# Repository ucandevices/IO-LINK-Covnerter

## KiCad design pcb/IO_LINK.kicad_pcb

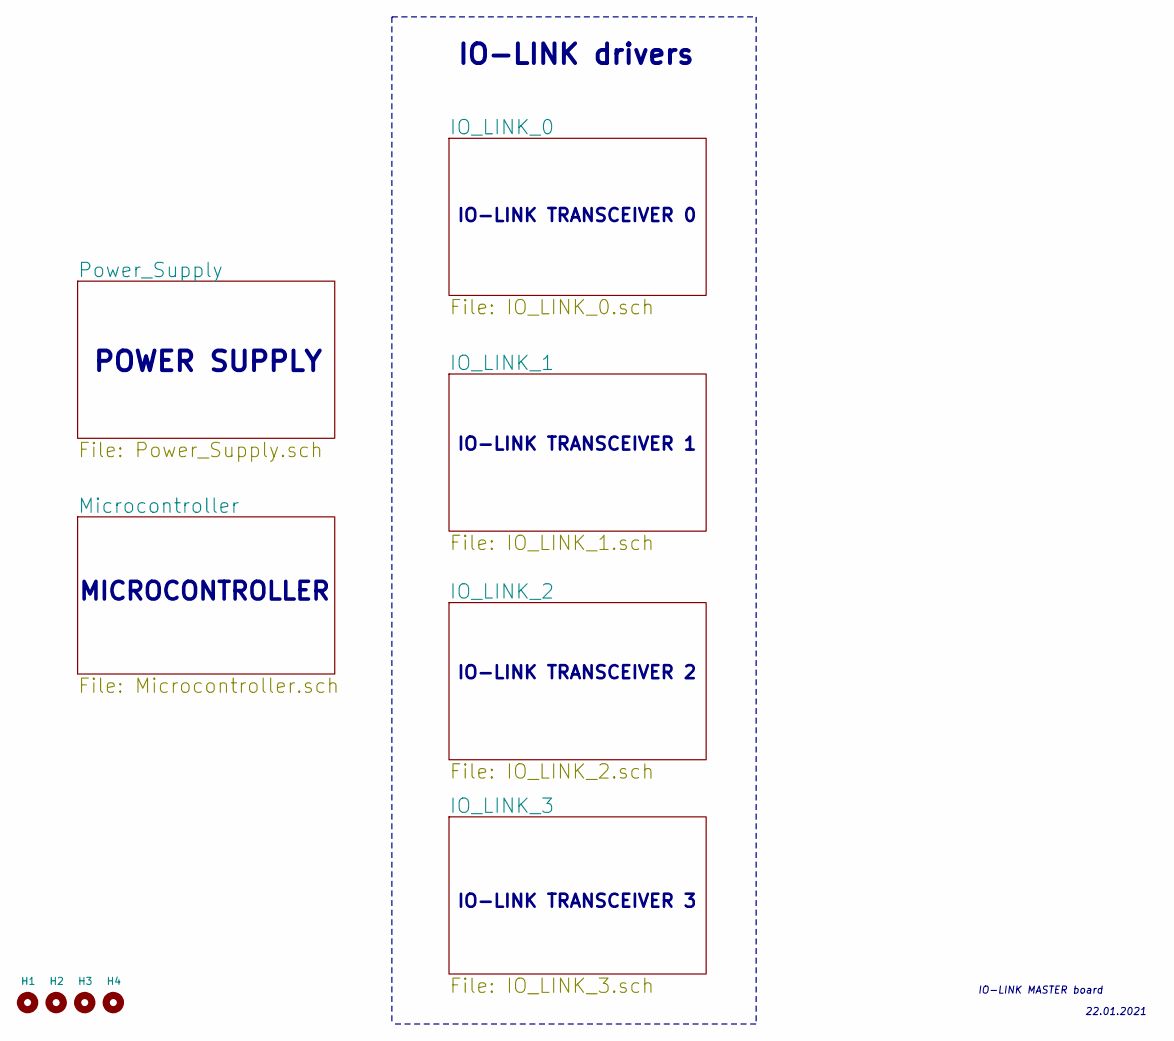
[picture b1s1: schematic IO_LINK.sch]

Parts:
H1, H2, H3, H4: MountingHole; MountingHole_3.2mm_M3_ISO14580_Pad_TopBottom

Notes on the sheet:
POWER SUPPLY
IO-LINK drivers
MICROCONTROLLER
IO-LINK TRANSCEIVER 0
IO-LINK TRANSCEIVER 1
IO-LINK TRANSCEIVER 2
IO-LINK TRANSCEIVER 3
IO-LINK MASTER board
22.01.2021

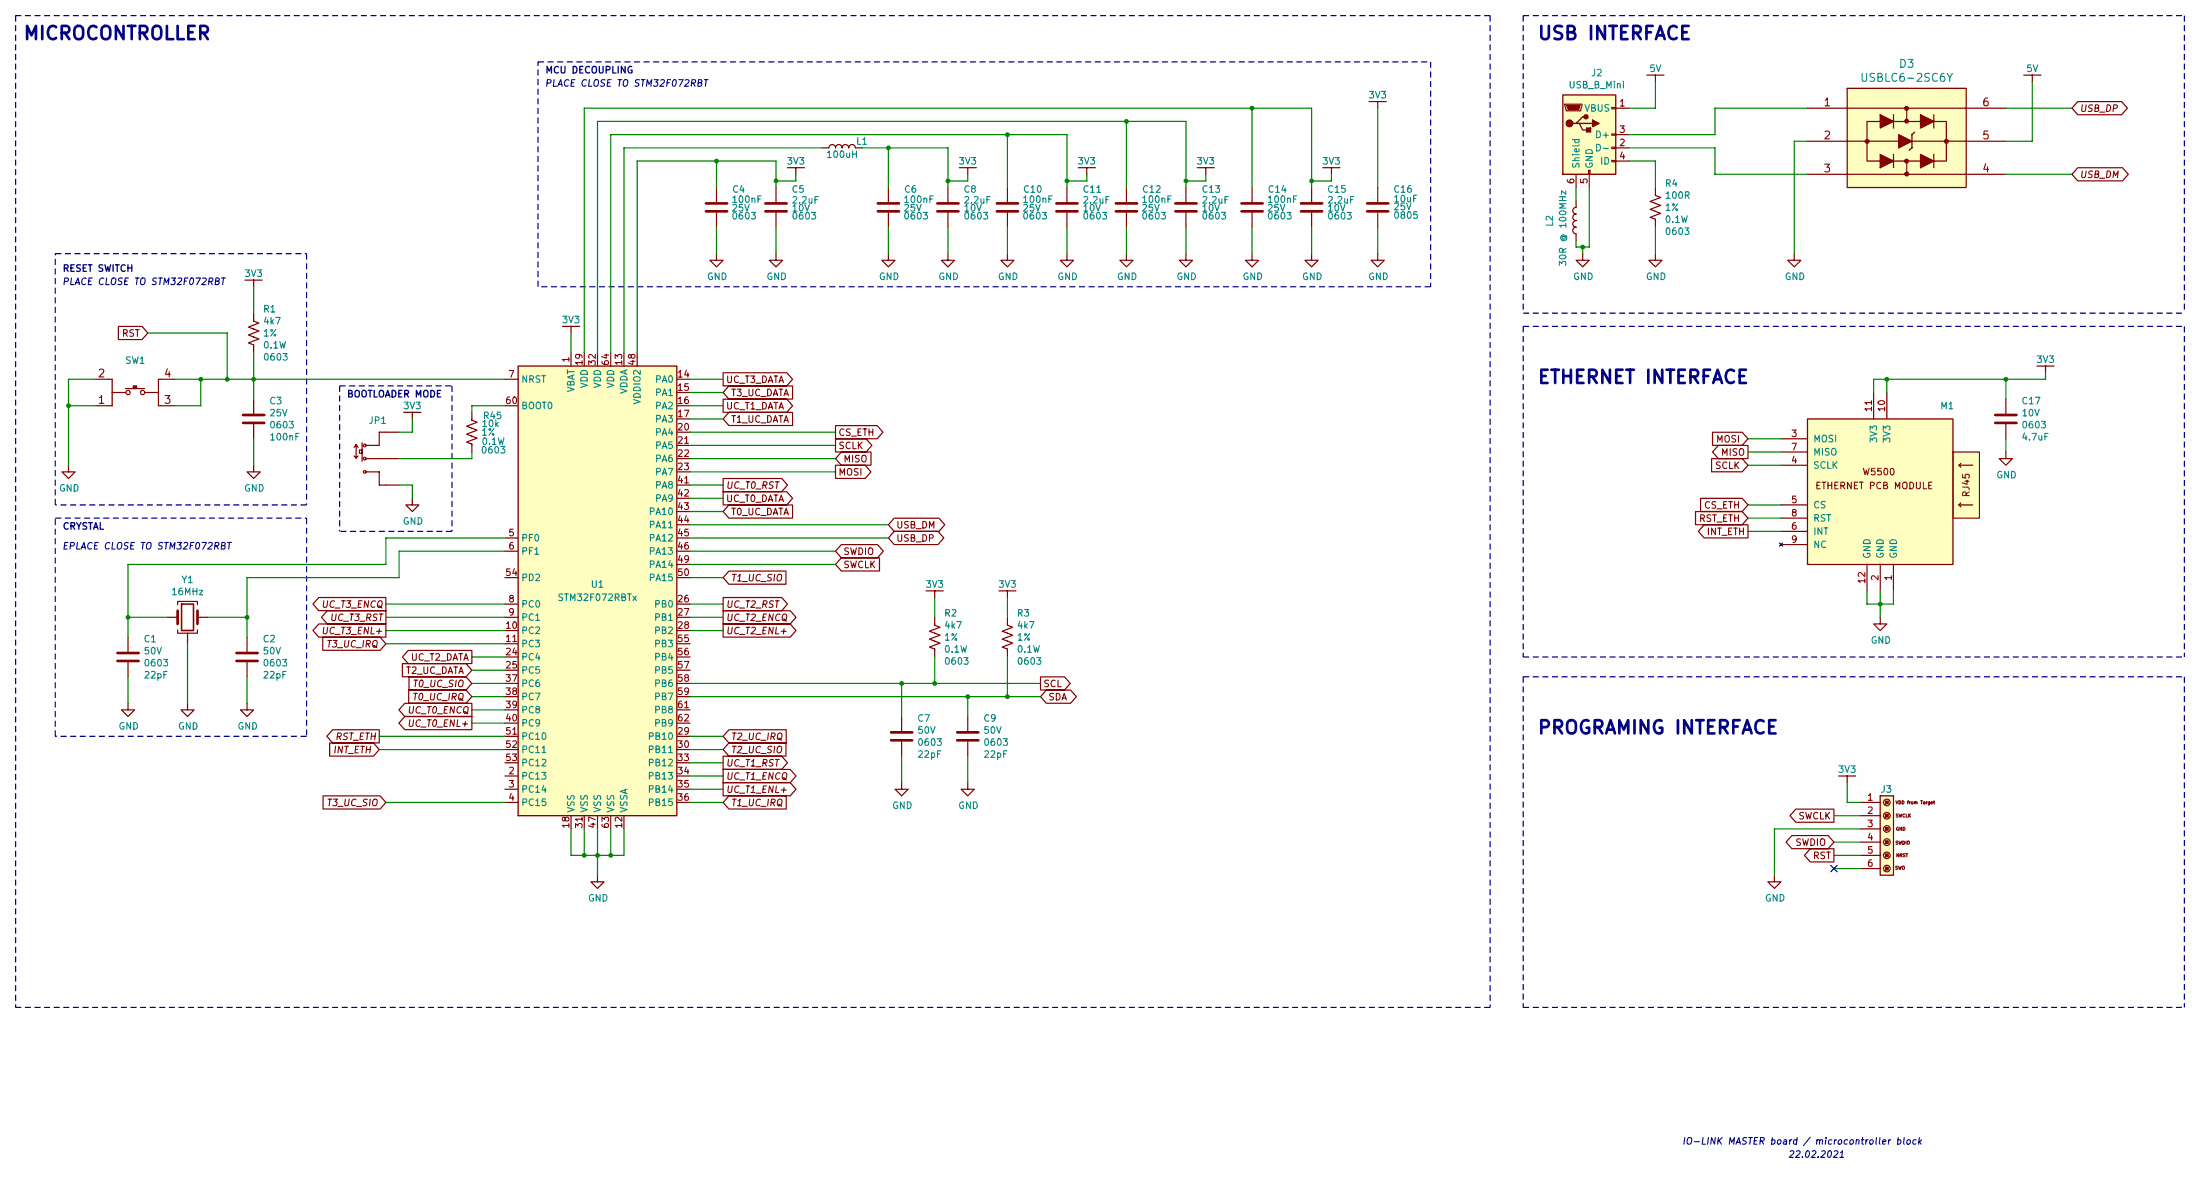
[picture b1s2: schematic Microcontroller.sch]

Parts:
C1, C2, C7, C9: 22pF_50V_0603; C_0603_1608Metric_Pad1.08x0.95mm_HandSolder; Voltage 50V; MPN CL10C220JB8NNNC; LCSC C1653
C3, C4, C6, C10, C12, C14: 100nF_25V_0603; C_0603_1608Metric_Pad1.08x0.95mm_HandSolder; Voltage 25V; MPN 0603B104K250CT; LCSC C83054
C5, C8, C11, C13, C15: 2.2uF_10V_0603; C_0603_1608Metric_Pad1.08x0.95mm_HandSolder; Voltage 10V; MPN CL10A225KP8NNNC; LCSC C1607
C16: 10uF_25V_0805; C_0805_2012Metric_Pad1.18x1.45mm_HandSolder; Voltage 25V; MPN CL21A106KAYNNNE; LCSC C15850
C17: 4.7uF_10V_0603; C_0603_1608Metric_Pad1.08x0.95mm_HandSolder; Voltage 10V; MPN CL10A475KP8NNNC; LCSC C1705
D3: USBLC6-2SC6Y; SOT-23-6L; MPN USBLC6-2SC6Y; LCSC C435848
J2: USB_B_Mini; USB_Mini-B_Horizontal; MPN 10033526-N3222MLF; LCSC N/A
J3: STM_PROGRAMING_CONNECTOR; MPN T821120A1S100CEU; LCSC N/A
JP1: SOLDERED_SELECTOR; SOLDERABLE_SELECTOR; MPN MCU08050Z0000ZP500; LCSC N/a
L1: Coil_100uH_0805; COIL_0805; MPN KLZ2012NHR101LTD25; LCSC N/A
L2: FB_30R@100MHz; Ferrite_bead_0603; MPN BLM18SP300SZ1D; LCSC N/A
M1: W5500_ETHERNET_PCB_MODULE; W5500_LITE_PCB_MODULE; MPN N/A; LCSC N/A
R1, R2, R3: 4k7_1%_0.1W_0603; R_0603_1608Metric_Pad0.98x0.95mm_HandSolder; Tolerance 1%; MPN 0603WAF4701T5E; LCSC C23162
R4: 100R_1%_0.1W_0603; R_0603_1608Metric_Pad0.98x0.95mm_HandSolder; Tolerance 1%; MPN 0603WAF1000T5E; LCSC C22775
R45: 10k_1%_0.1W_0603; R_0603_1608Metric_Pad0.98x0.95mm_HandSolder; Tolerance 1%; MPN 0603WAF1002T5E; LCSC C25804
SW1: Tactile_Switch; MPN PTS647SN50SMTR2LFS; LCSC N/A
U1: STM32F072RBTx; LQFP-64_10x10mm_P0.5mm
Y1: CRYSTAL_16MHz_4PADS; CRYSTAL_SMD_4PADS_3.2x2.5; MPN X322516MLB4SI; LCSC C13738

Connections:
3V3: C4.1, C5.1, C6.1, C8.1, C10.1, C11.1, C12.1, C13.1, C14.1, C15.1, C16.1, C17.1, J3.1, JP1.1, L1.2, M1.10 (3V3), M1.11 (3V3), R1.1, R2.1, R3.1, U1.1 (VBAT), U1.19 (VDD), U1.32 (VDD), U1.48 (VDDIO2), U1.64 (VDD); also elsewhere on the board
5V: D3.5, J2.1 (VBUS)
CS_ETH: M1.5 (CS), U1.20 (PA4)
GND: C1.2, C2.2, C3.2, C4.2, C5.2, C6.2, C7.2, C8.2, C9.2, C10.2, C11.2, C12.2, C13.2, C14.2, C15.2, C16.2, C17.2, D3.2, J2.5 (GND), J3.3, JP1.3, L2.1, M1.1 (GND), M1.2 (GND), M1.12 (GND), R4.2, SW1.1, SW1.2, U1.12 (VSSA), U1.18 (VSS), U1.31 (VSS), U1.47 (VSS), U1.63 (VSS), Y1.3; also elsewhere on the board
INT_ETH: M1.6 (INT), U1.52 (PC11)
MISO: M1.7 (MISO), U1.22 (PA6)
MOSI: M1.3 (MOSI), U1.23 (PA7)
unnamed: C1.1, U1.5 (PF0), Y1.1
unnamed: C2.1, U1.6 (PF1), Y1.2
unnamed: D3.1 (/IO), J2.3 (D+)
unnamed: D3.3 (2/IO), J2.2 (D-)
unnamed: J2.4 (ID), R4.1
unnamed: J2.6 (Shield), L2.2
unnamed: JP1.2, R45.2
unnamed: L1.1, U1.13 (VDDA)
unnamed: R45.1, U1.60 (BOOT0)
RST: C3.1, J3.5, R1.2, SW1.3, SW1.4, U1.7 (NRST)
RST_ETH: M1.8 (RST), U1.51 (PC10)
SCL: C7.1, R2.2, U1.58 (PB6); also elsewhere on the board
SCLK: M1.4 (SCLK), U1.21 (PA5)
SDA: C9.1, R3.2, U1.59 (PB7); also elsewhere on the board
SWCLK: J3.2, U1.49 (PA14)
SWDIO: J3.4, U1.46 (PA13)
T0_UC_DATA: U1.43 (PA10); also elsewhere on the board
T0_UC_IRQ: U1.38 (PC7); also elsewhere on the board
T0_UC_SIO: U1.37 (PC6); also elsewhere on the board
T1_UC_DATA: U1.17 (PA3); also elsewhere on the board
T1_UC_IRQ: U1.36 (PB15); also elsewhere on the board
T1_UC_SIO: U1.50 (PA15); also elsewhere on the board
T2_UC_DATA: U1.25 (PC5); also elsewhere on the board
T2_UC_IRQ: U1.29 (PB10); also elsewhere on the board
T2_UC_SIO: U1.30 (PB11); also elsewhere on the board
T3_UC_DATA: U1.15 (PA1); also elsewhere on the board
T3_UC_IRQ: U1.11 (PC3); also elsewhere on the board
T3_UC_SIO: U1.4 (PC15); also elsewhere on the board
UC_T0_DATA: U1.42 (PA9); also elsewhere on the board
UC_T0_ENCQ: U1.39 (PC8); also elsewhere on the board
UC_T0_ENL+: U1.40 (PC9); also elsewhere on the board
UC_T0_RST: U1.41 (PA8); also elsewhere on the board
UC_T1_DATA: U1.16 (PA2); also elsewhere on the board
UC_T1_ENCQ: U1.34 (PB13); also elsewhere on the board
UC_T1_ENL+: U1.35 (PB14); also elsewhere on the board
UC_T1_RST: U1.33 (PB12); also elsewhere on the board
UC_T2_DATA: U1.24 (PC4); also elsewhere on the board
UC_T2_ENCQ: U1.27 (PB1); also elsewhere on the board
UC_T2_ENL+: U1.28 (PB2); also elsewhere on the board
UC_T2_RST: U1.26 (PB0); also elsewhere on the board
UC_T3_DATA: U1.14 (PA0); also elsewhere on the board
UC_T3_ENCQ: U1.8 (PC0); also elsewhere on the board
UC_T3_ENL+: U1.10 (PC2); also elsewhere on the board
UC_T3_RST: U1.9 (PC1); also elsewhere on the board
USB_DM: D3.4 (2/IO), U1.44 (PA11)
USB_DP: D3.6 (1/IO), U1.45 (PA12)

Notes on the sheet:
USB INTERFACE
ETHERNET INTERFACE
RESET SWITCH
PROGRAMING INTERFACE
PLACE CLOSE TO STM32F072RBT
EPLACE CLOSE TO STM32F072RBT
CRYSTAL
MCU DECOUPLING
BOOTLOADER MODE
MICROCONTROLLER
IO-LINK MASTER board / microcontroller block
22.02.2021

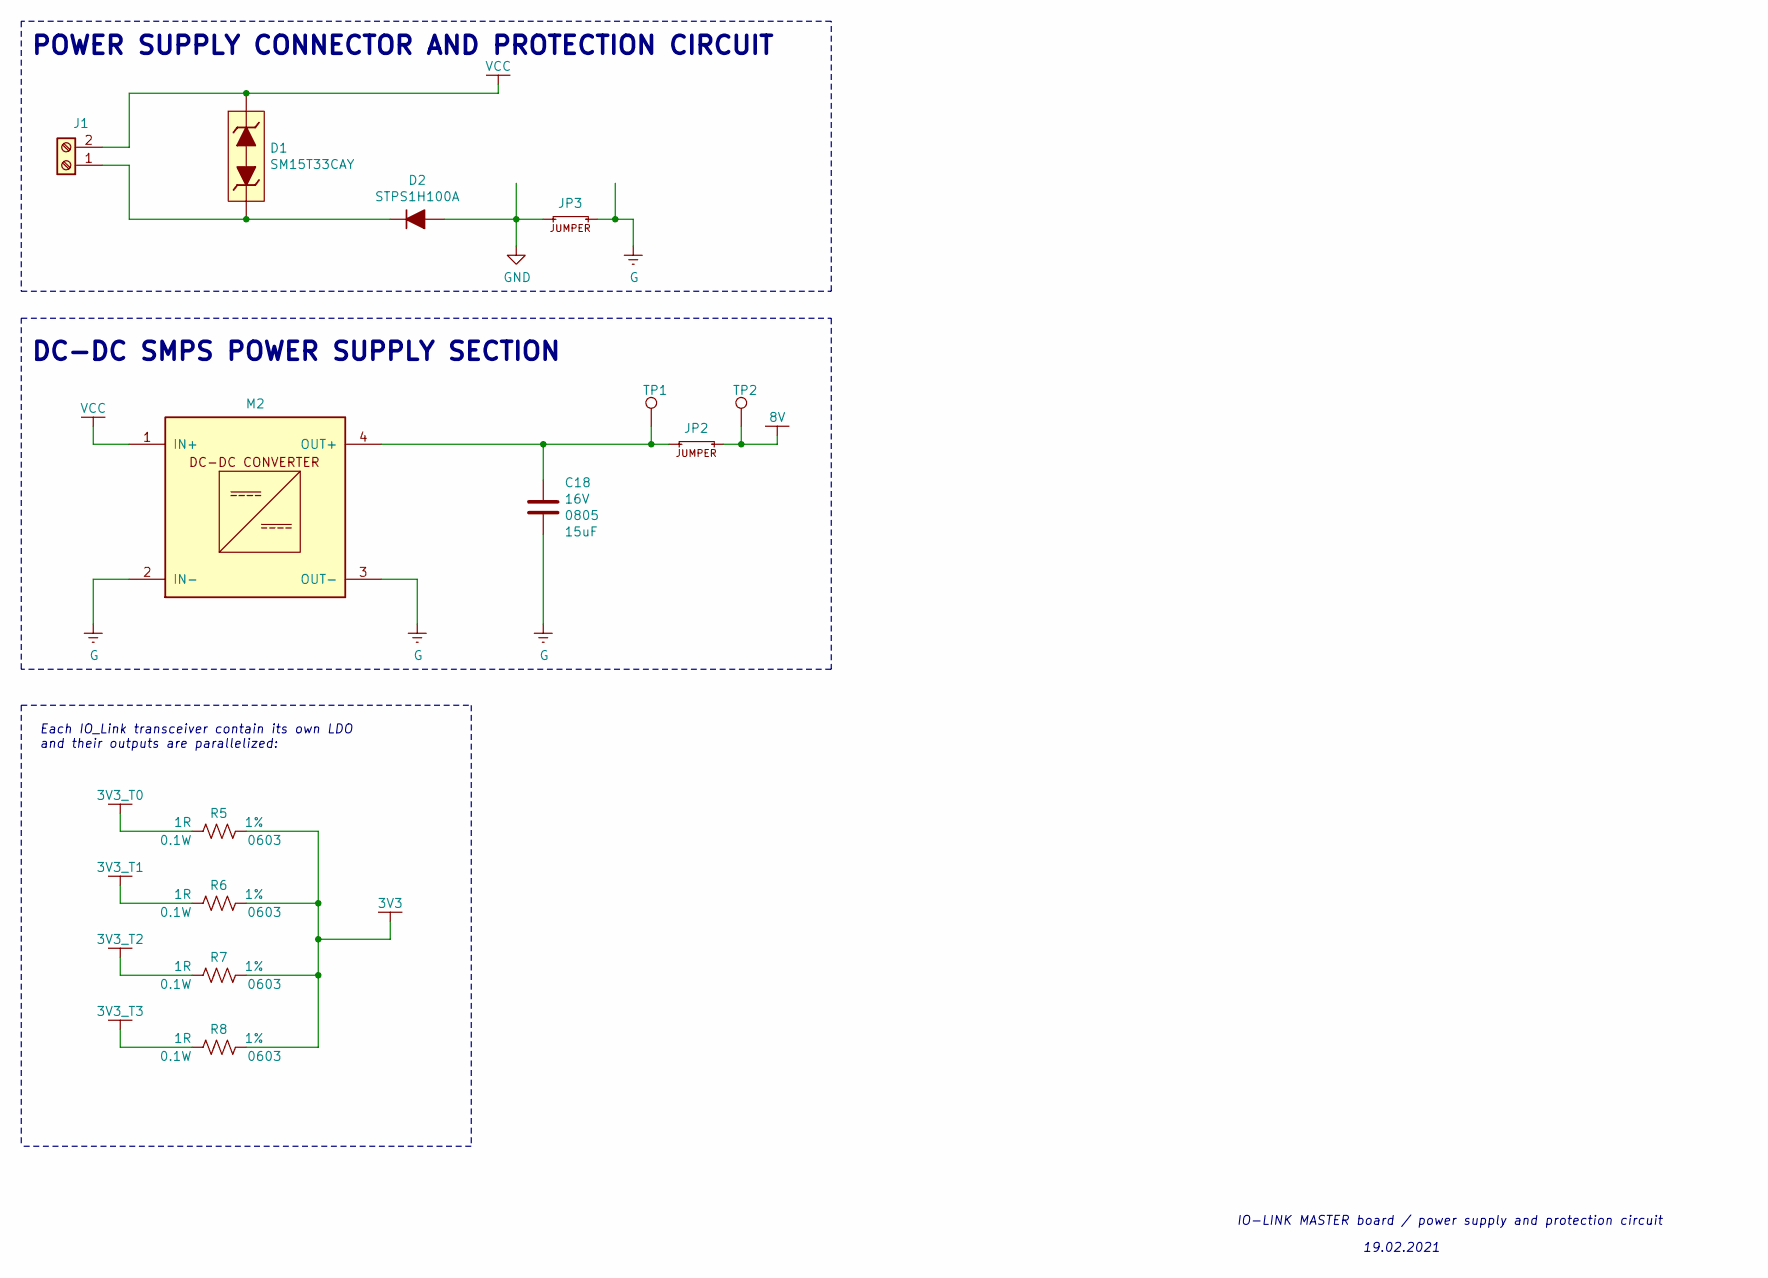
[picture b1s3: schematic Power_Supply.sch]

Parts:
C18: 15uF_16V_0805; C_0805_2012Metric_Pad1.18x1.45mm_HandSolder; Voltage 16V; MPN C2012JB1C156M125AC; LCSC N/A
D1: SM15T33CAY; SMC_BI_TVS; MPN SM15T33CAY; LCSC N/A
D2: STPS1H100A; SMA; MPN STPS1H100A; LCSC N/A
J1: Screw_Terminal_01x02; TerminalBlock_Altech_AK300-2_P5.00mm; MPN 1729128; LCSC N/A
JP2: 0R_1%_0.1W_0805; R_0805_2012Metric_Pad1.20x1.40mm_HandSolder; Tolerance 1%; MPN 0805W8F0000T5E; LCSC C17477
JP3: JUMPER_0805; R_0805_2012Metric_Pad1.20x1.40mm_HandSolder; Tolerance 1%; MPN 0805W8F0000T5E; LCSC C17477
M2: DC_DC_CONVERTER_LM2596_PCB_MODULE; MPN N/A; LCSC N/A
R5, R6, R7, R8: 1R_1%_0.1W_0603; R_0603_1608Metric_Pad0.98x0.95mm_HandSolder; Tolerance 1%; MPN 0603WAF100KT5E; LCSC C22936
TP1, TP2: TestPoint; TestPoint_Pad_D2.0mm

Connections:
3V3: R5.2, R6.2, R7.2, R8.2; also elsewhere on the board
3V3_T0: R5.1; also elsewhere on the board
3V3_T1: R6.1; also elsewhere on the board
3V3_T2: R7.1; also elsewhere on the board
3V3_T3: R8.1; also elsewhere on the board
8V: JP2.2, TP2.1; also elsewhere on the board
G: C18.2, JP3.2, M2.2 (IN-), M2.3 (OUT-); also elsewhere on the board
GND: D2.2 (A), JP3.1; also elsewhere on the board
unnamed: C18.1, JP2.1, M2.4 (OUT+), TP1.1
unnamed: D1.1, D2.1 (K), J1.1
VCC: D1.2, J1.2, M2.1 (IN+); also elsewhere on the board

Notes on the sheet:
POWER SUPPLY CONNECTOR AND PROTECTION CIRCUIT
IO-LINK MASTER board / power supply and protection circuit
19.02.2021
DC-DC SMPS POWER SUPPLY SECTION
Each IO_Link transceiver contain its own LDO and their outputs are parallelized:

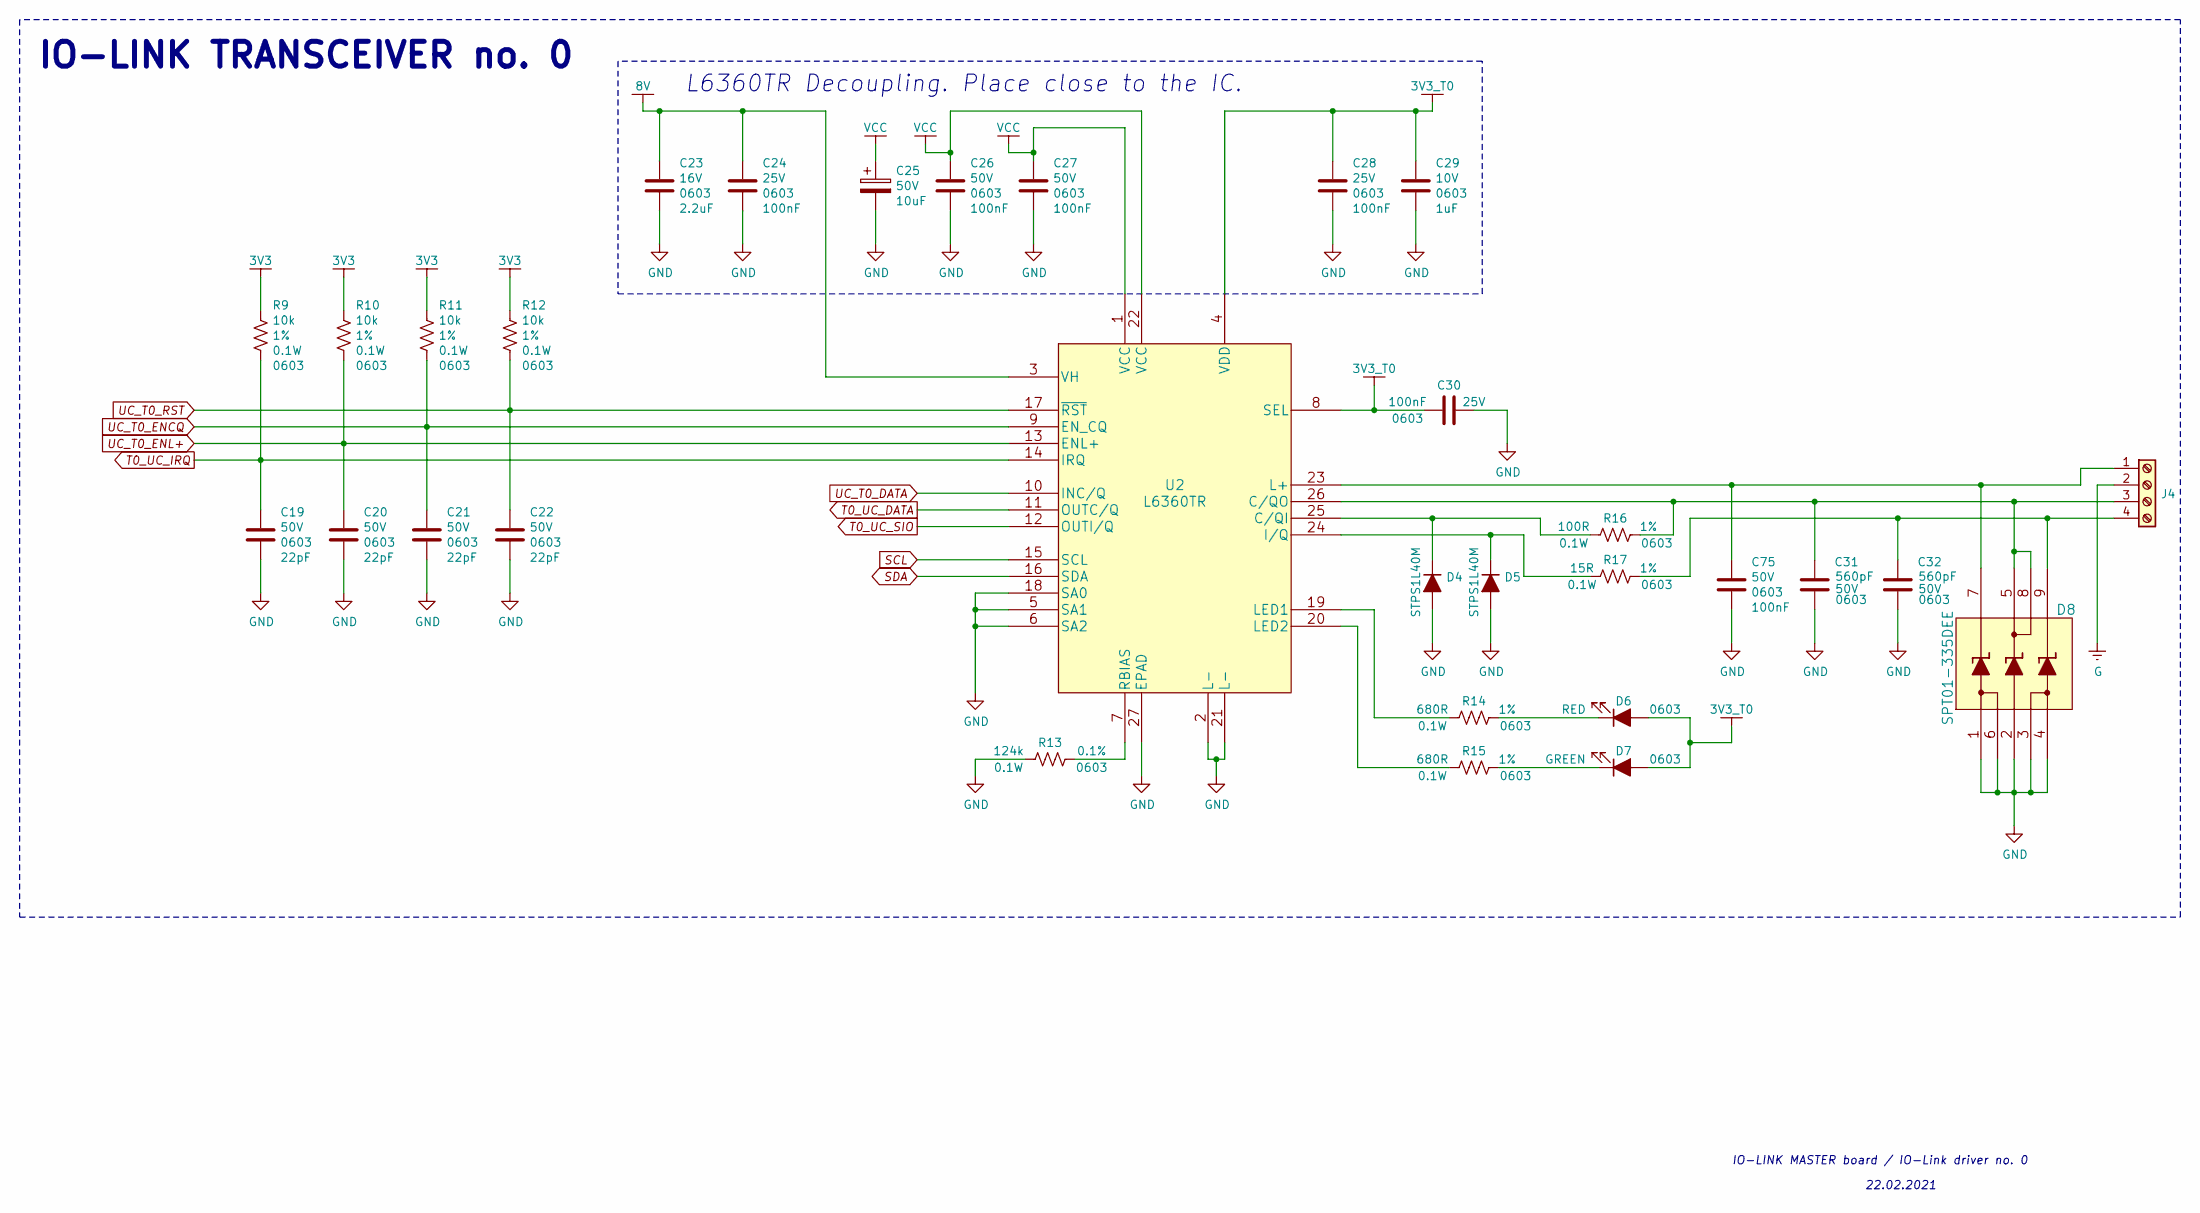
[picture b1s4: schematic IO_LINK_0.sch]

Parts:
C19, C20, C21, C22: 22pF_50V_0603; C_0603_1608Metric_Pad1.08x0.95mm_HandSolder; Voltage 50V; MPN CL10C220JB8NNNC; LCSC C1653
C23: 2.2uF_16V_0603; C_0603_1608Metric_Pad1.08x0.95mm_HandSolder; Voltage 16V; MPN CL10A225KO8NNNC; LCSC C23630
C24, C28, C30: 100nF_25V_0603; C_0603_1608Metric_Pad1.08x0.95mm_HandSolder; Voltage 25V; MPN 0603B104K250CT; LCSC C83054
C25: 10uF_50V_6.3mm_x_5.8mm_electrolytic; CP_Elec_6.3x5.8; Voltage 50V; MPN VZH100M1HTR-0606; LCSC C249820
C26, C27, C75: 100nF_50V_0603; C_0603_1608Metric_Pad1.08x0.95mm_HandSolder; Voltage 50V; MPN CC0603KRX7R9BB104; LCSC C14663
C29: 1uF_10V_0603; C_0603_1608Metric_Pad1.08x0.95mm_HandSolder; Voltage 10V; MPN CL10B105KP8NNNC; LCSC C95843
C31, C32: 560pF_50V_0603; C_0603_1608Metric_Pad1.08x0.95mm_HandSolder; Voltage 50V; MPN CL10B561KB8NNNC; LCSC C84721
D4, D5: STPS1L40M; DO-216; MPN STPS1L40M; LCSC N/A
D6: LED_RED; LED_0603; MPN 150060RS55040; LCSC N/A
D7: LED_GREEN; LED_0603; MPN 150060VS55040; LCSC N/A
D8: SPT01-335DEE; MPN SPT01-335DEE; LCSC N/A
J4: Screw_Terminal_01x04; TerminalBlock_Altech_AK300-4_P5.00mm; MPN 1715747; LCSC N/A
R9, R10, R11, R12: 10k_1%_0.1W_0603; R_0603_1608Metric_Pad0.98x0.95mm_HandSolder; Tolerance 1%; MPN 0603WAF1002T5E; LCSC C25804
R13: 124k_0.1%_0.1W_0603; R_0603_1608Metric_Pad0.98x0.95mm_HandSolder; Tolerance 0.1%; MPN RG1608P-1243-B-T5; LCSC N/A
R14, R15: 680R_1%_0.1W_0603; R_0603_1608Metric_Pad0.98x0.95mm_HandSolder; Tolerance 1%; MPN 0603WAF6800T5E; LCSC C23228
R16: 100R_1%_0.1W_0603; R_0603_1608Metric_Pad0.98x0.95mm_HandSolder; Tolerance 1%; MPN 0603WAF1000T5E; LCSC C22775
R17: 15R_1%_0.1W_0603; R_0603_1608Metric_Pad0.98x0.95mm_HandSolder; Tolerance 1%; MPN 0603WAF150JT5E; LCSC C22810
U2: L6360TR; MPN L6360TR; LCSC N/A

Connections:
3V3: R9.1, R10.1, R11.1, R12.1; also elsewhere on the board
3V3_T0: C28.1, C29.1, C30.2, D6.2 (A), D7.2 (A), U2.4 (VDD), U2.8 (SEL); also elsewhere on the board
8V: C23.1, C24.1, U2.3 (VH); also elsewhere on the board
G: J4.2; also elsewhere on the board
GND: C19.2, C20.2, C21.2, C22.2, C23.2, C24.2, C25.2, C26.2, C27.2, C28.2, C29.2, C30.1, C31.2, C32.2, C75.2, D4.2 (A), D5.2 (A), D8.1, D8.2, D8.3, D8.4, D8.6, R13.2, U2.2 (L-), U2.5 (SA1), U2.6 (SA2), U2.18 (SA0), U2.21 (L-), U2.27 (EPAD); also elsewhere on the board
unnamed: C31.1, D8.5, D8.8, J4.3, R16.1, U2.26 (C/QO)
unnamed: C32.1, D8.9, J4.4, R17.1
unnamed: C75.1, D8.7, J4.1, U2.23 (L+)
unnamed: D4.1 (K), R16.2, U2.25 (C/QI)
unnamed: D5.1 (K), R17.2, U2.24 (I/Q)
unnamed: D6.1 (K), R14.1
unnamed: D7.1 (K), R15.1
unnamed: R13.1, U2.7 (RBIAS)
unnamed: R14.2, U2.19 (LED1)
unnamed: R15.2, U2.20 (LED2)
SCL: U2.15 (SCL); also elsewhere on the board
SDA: U2.16 (SDA); also elsewhere on the board
T0_UC_DATA: U2.11 (OUTC/Q); also elsewhere on the board
T0_UC_IRQ: C19.1, R9.2, U2.14 (IRQ); also elsewhere on the board
T0_UC_SIO: U2.12 (OUTI/Q); also elsewhere on the board
UC_T0_DATA: U2.10 (INC/Q); also elsewhere on the board
UC_T0_ENCQ: C21.1, R11.2, U2.9 (EN_CQ); also elsewhere on the board
UC_T0_ENL+: C20.1, R10.2, U2.13 (ENL+); also elsewhere on the board
UC_T0_RST: C22.1, R12.2, U2.17 (~RST); also elsewhere on the board
VCC: C25.1, C26.1, C27.1, U2.1 (VCC), U2.22 (VCC); also elsewhere on the board

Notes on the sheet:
L6360TR Decoupling. Place close to the IC.
IO-LINK TRANSCEIVER no. 0
IO-LINK MASTER board / IO-Link driver no. 0
22.02.2021

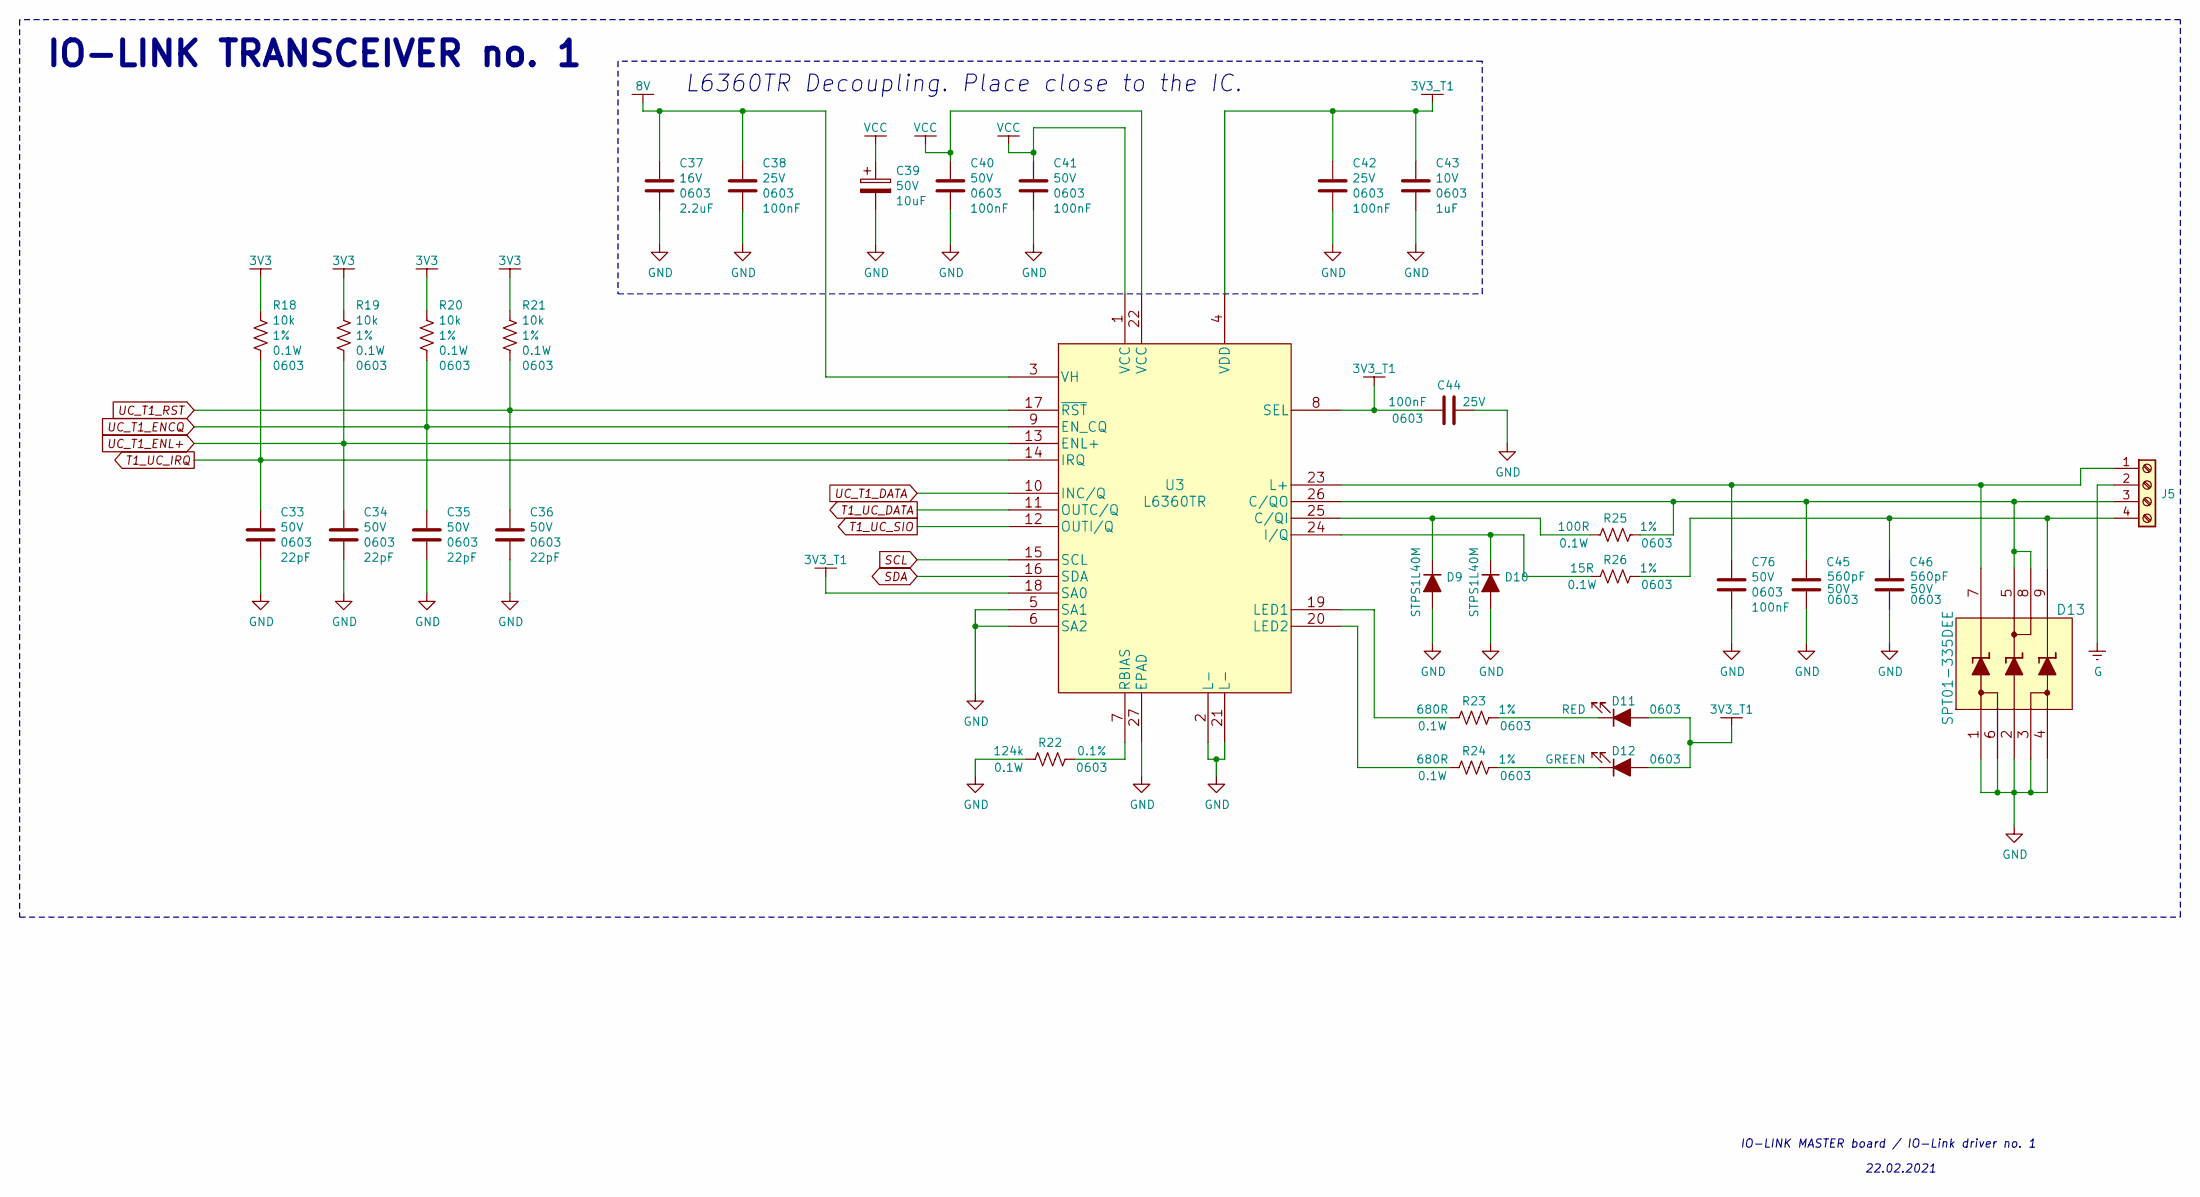
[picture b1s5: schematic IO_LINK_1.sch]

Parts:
C33, C34, C35, C36: 22pF_50V_0603; C_0603_1608Metric_Pad1.08x0.95mm_HandSolder; Voltage 50V; MPN CL10C220JB8NNNC; LCSC C1653
C37: 2.2uF_16V_0603; C_0603_1608Metric_Pad1.08x0.95mm_HandSolder; Voltage 16V; MPN CL10A225KO8NNNC; LCSC C23630
C38, C42, C44: 100nF_25V_0603; C_0603_1608Metric_Pad1.08x0.95mm_HandSolder; Voltage 25V; MPN 0603B104K250CT; LCSC C83054
C39: 10uF_50V_6.3mm_x_5.8mm_electrolytic; CP_Elec_6.3x5.8; Voltage 50V; MPN VZH100M1HTR-0606; LCSC C249820
C40, C41, C76: 100nF_50V_0603; C_0603_1608Metric_Pad1.08x0.95mm_HandSolder; Voltage 50V; MPN CC0603KRX7R9BB104; LCSC C14663
C43: 1uF_10V_0603; C_0603_1608Metric_Pad1.08x0.95mm_HandSolder; Voltage 10V; MPN CL10B105KP8NNNC; LCSC C95843
C45, C46: 560pF_50V_0603; C_0603_1608Metric_Pad1.08x0.95mm_HandSolder; Voltage 50V; MPN CL10B561KB8NNNC; LCSC C84721
D9, D10: STPS1L40M; DO-216; MPN STPS1L40M; LCSC N/A
D11: LED_RED; LED_0603; MPN 150060RS55040; LCSC N/A
D12: LED_GREEN; LED_0603; MPN 150060VS55040; LCSC N/A
D13: SPT01-335DEE; MPN SPT01-335DEE; LCSC N/A
J5: Screw_Terminal_01x04; TerminalBlock_Altech_AK300-4_P5.00mm; MPN 1715747; LCSC N/A
R18, R19, R20, R21: 10k_1%_0.1W_0603; R_0603_1608Metric_Pad0.98x0.95mm_HandSolder; Tolerance 1%; MPN 0603WAF1002T5E; LCSC C25804
R22: 124k_0.1%_0.1W_0603; R_0603_1608Metric_Pad0.98x0.95mm_HandSolder; Tolerance 0.1%; MPN RG1608P-1243-B-T5; LCSC N/A
R23, R24: 680R_1%_0.1W_0603; R_0603_1608Metric_Pad0.98x0.95mm_HandSolder; Tolerance 1%; MPN 0603WAF6800T5E; LCSC C23228
R25: 100R_1%_0.1W_0603; R_0603_1608Metric_Pad0.98x0.95mm_HandSolder; Tolerance 1%; MPN 0603WAF1000T5E; LCSC C22775
R26: 15R_1%_0.1W_0603; R_0603_1608Metric_Pad0.98x0.95mm_HandSolder; Tolerance 1%; MPN 0603WAF150JT5E; LCSC C22810
U3: L6360TR; MPN L6360TR; LCSC N/A

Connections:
3V3: R18.1, R19.1, R20.1, R21.1; also elsewhere on the board
3V3_T1: C42.1, C43.1, C44.2, D11.2 (A), D12.2 (A), U3.4 (VDD), U3.8 (SEL), U3.18 (SA0); also elsewhere on the board
8V: C37.1, C38.1, U3.3 (VH); also elsewhere on the board
G: J5.2; also elsewhere on the board
GND: C33.2, C34.2, C35.2, C36.2, C37.2, C38.2, C39.2, C40.2, C41.2, C42.2, C43.2, C44.1, C45.2, C46.2, C76.2, D9.2 (A), D10.2 (A), D13.1, D13.2, D13.3, D13.4, D13.6, R22.2, U3.2 (L-), U3.5 (SA1), U3.6 (SA2), U3.21 (L-), U3.27 (EPAD); also elsewhere on the board
unnamed: C45.1, D13.5, D13.8, J5.3, R25.1, U3.26 (C/QO)
unnamed: C46.1, D13.9, J5.4, R26.1
unnamed: C76.1, D13.7, J5.1, U3.23 (L+)
unnamed: D9.1 (K), R25.2, U3.25 (C/QI)
unnamed: D10.1 (K), R26.2, U3.24 (I/Q)
unnamed: D11.1 (K), R23.1
unnamed: D12.1 (K), R24.1
unnamed: R22.1, U3.7 (RBIAS)
unnamed: R23.2, U3.19 (LED1)
unnamed: R24.2, U3.20 (LED2)
SCL: U3.15 (SCL); also elsewhere on the board
SDA: U3.16 (SDA); also elsewhere on the board
T1_UC_DATA: U3.11 (OUTC/Q); also elsewhere on the board
T1_UC_IRQ: C33.1, R18.2, U3.14 (IRQ); also elsewhere on the board
T1_UC_SIO: U3.12 (OUTI/Q); also elsewhere on the board
UC_T1_DATA: U3.10 (INC/Q); also elsewhere on the board
UC_T1_ENCQ: C35.1, R20.2, U3.9 (EN_CQ); also elsewhere on the board
UC_T1_ENL+: C34.1, R19.2, U3.13 (ENL+); also elsewhere on the board
UC_T1_RST: C36.1, R21.2, U3.17 (~RST); also elsewhere on the board
VCC: C39.1, C40.1, C41.1, U3.1 (VCC), U3.22 (VCC); also elsewhere on the board

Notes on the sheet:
L6360TR Decoupling. Place close to the IC.
IO-LINK TRANSCEIVER no. 1
IO-LINK MASTER board / IO-Link driver no. 1
22.02.2021
